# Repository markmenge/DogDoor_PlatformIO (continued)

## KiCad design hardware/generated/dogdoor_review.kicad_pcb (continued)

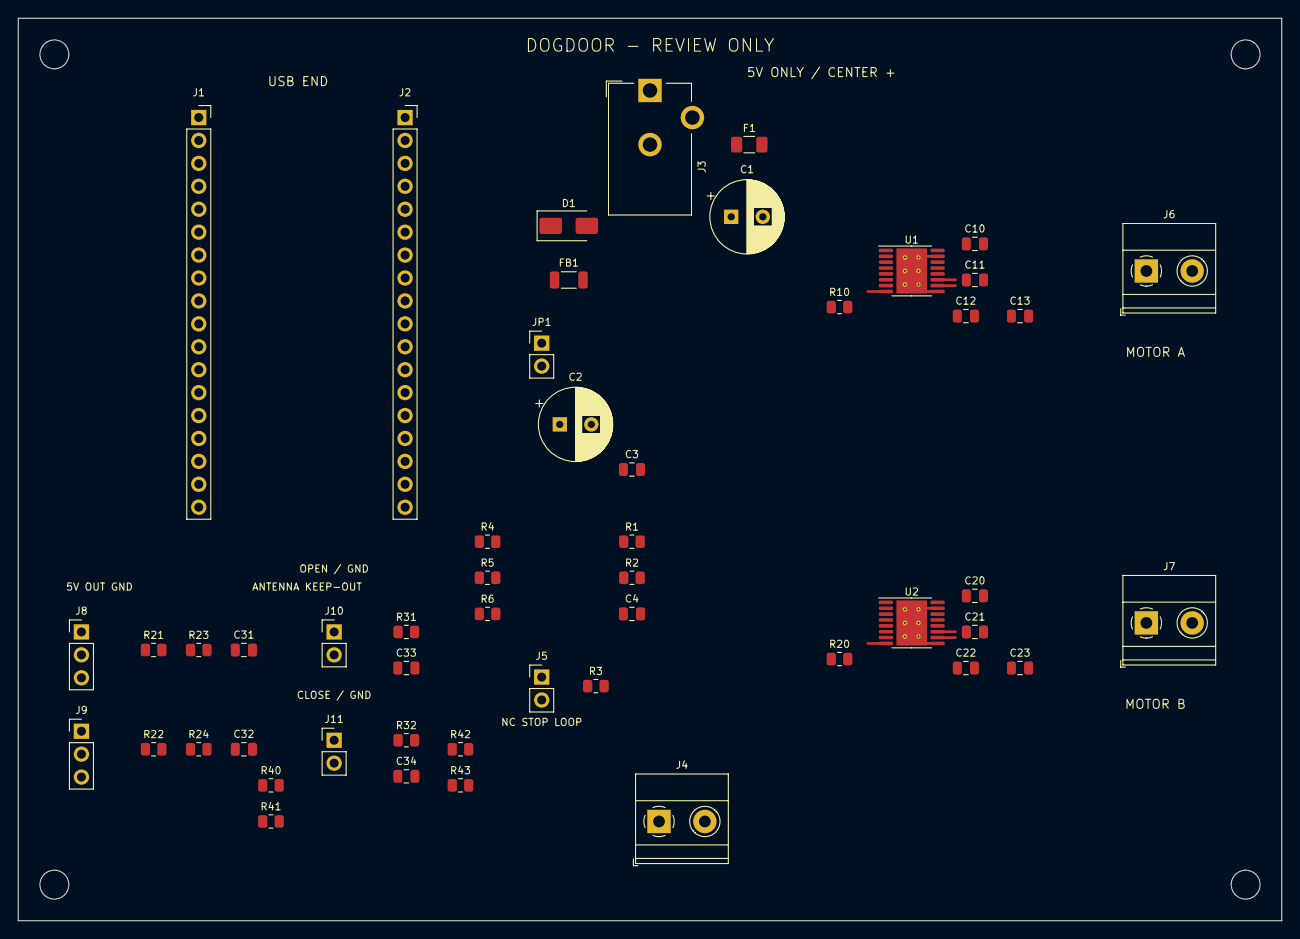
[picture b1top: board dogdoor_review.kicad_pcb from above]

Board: 2 copper layers, 140.0 x 100.0 mm, 55 parts (0 on the bottom side), 36 nets.

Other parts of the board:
H1, H2, H3, H4: MountingHole_3.2mm_M3

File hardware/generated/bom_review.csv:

Reference,Value,Footprint,Assembly,MPN,Populate
J1,Heltec V2 LEFT,Connector_PinSocket_2.54mm:PinSocket_1x18_P2.54mm_Vertical,HAND,REVIEW_REQUIRED,True
J2,Heltec V2 RIGHT,Connector_PinSocket_2.54mm:PinSocket_1x18_P2.54mm_Vertical,HAND,REVIEW_REQUIRED,True
J3,5V 3A CENTER POSITIVE,Connector_BarrelJack:BarrelJack_CUI_PJ-102AH_Horizontal,HAND,PJ-102AH,True
F1,3A fuse - inrush review,Fuse:Fuse_1206_3216Metric,SMD,0467003.NR,True
D1,SS34 controller isolation,Diode_SMD:D_SMA,SMD,SS34,True
FB1,Ferrite >=1A low DCR,Inductor_SMD:L_1206_3216Metric,SMD,REVIEW_REQUIRED,True
JP1,REMOVE FOR USB POWER,Connector_PinHeader_2.54mm:PinHeader_1x02_P2.54mm_Vertical,HAND,REVIEW_REQUIRED,True
J4,POWER ALT + GND,"TerminalBlock_Phoenix:TerminalBlock_Phoenix_MKDS-1,5-2-5.08_1x02_P5.08mm_Horizontal",HAND,REVIEW_REQUIRED,True
C1,470uF 10V low ESR,Capacitor_THT:CP_Radial_D8.0mm_P3.50mm,HAND,REVIEW_REQUIRED,True
C2,470uF 10V low ESR,Capacitor_THT:CP_Radial_D8.0mm_P3.50mm,HAND,REVIEW_REQUIRED,True
C3,100nF 25V X7R,Capacitor_SMD:C_0805_2012Metric,SMD,REVIEW_REQUIRED,True
R1,10k 1%,Resistor_SMD:R_0805_2012Metric,SMD,REVIEW_REQUIRED,True
R2,10k 1%,Resistor_SMD:R_0805_2012Metric,SMD,REVIEW_REQUIRED,True
C4,100nF 25V X7R,Capacitor_SMD:C_0805_2012Metric,SMD,REVIEW_REQUIRED,True
J5,NC STOP LOOP - OPEN DISABLES BOTH,Connector_PinHeader_2.54mm:PinHeader_1x02_P2.54mm_Vertical,HAND,REVIEW_REQUIRED,True
R3,100k,Resistor_SMD:R_0805_2012Metric,SMD,REVIEW_REQUIRED,True
R4,47k,Resistor_SMD:R_0805_2012Metric,SMD,REVIEW_REQUIRED,True
R5,47k,Resistor_SMD:R_0805_2012Metric,SMD,REVIEW_REQUIRED,True
R6,10k,Resistor_SMD:R_0805_2012Metric,SMD,REVIEW_REQUIRED,True
U1,DRV8876PWPR,Package_SO:HTSSOP-16-1EP_4.4x5mm_P0.65mm_EP3.4x5mm_Mask2.46x2.31mm_ThermalVias,SMD,DRV8876PWPR,True
C10,22nF 25V X7R,Capacitor_SMD:C_0805_2012Metric,SMD,REVIEW_REQUIRED,True
C11,100nF 25V X7R,Capacitor_SMD:C_0805_2012Metric,SMD,REVIEW_REQUIRED,True
C12,100nF 25V X7R,Capacitor_SMD:C_0805_2012Metric,SMD,REVIEW_REQUIRED,True
C13,10uF 16V X7R,Capacitor_SMD:C_0805_2012Metric,SMD,REVIEW_REQUIRED,True
R10,1.50k 1% ~1A trip,Resistor_SMD:R_0805_2012Metric,SMD,REVIEW_REQUIRED,True
J6,MOTOR A,"TerminalBlock_Phoenix:TerminalBlock_Phoenix_MKDS-1,5-2-5.08_1x02_P5.08mm_Horizontal",HAND,REVIEW_REQUIRED,True
U2,DRV8876PWPR,Package_SO:HTSSOP-16-1EP_4.4x5mm_P0.65mm_EP3.4x5mm_Mask2.46x2.31mm_ThermalVias,SMD,DRV8876PWPR,True
C20,22nF 25V X7R,Capacitor_SMD:C_0805_2012Metric,SMD,REVIEW_REQUIRED,True
C21,100nF 25V X7R,Capacitor_SMD:C_0805_2012Metric,SMD,REVIEW_REQUIRED,True
C22,100nF 25V X7R,Capacitor_SMD:C_0805_2012Metric,SMD,REVIEW_REQUIRED,True
C23,10uF 16V X7R,Capacitor_SMD:C_0805_2012Metric,SMD,REVIEW_REQUIRED,True
R20,1.50k 1% ~1A trip,Resistor_SMD:R_0805_2012Metric,SMD,REVIEW_REQUIRED,True
J7,MOTOR B,"TerminalBlock_Phoenix:TerminalBlock_Phoenix_MKDS-1,5-2-5.08_1x02_P5.08mm_Horizontal",HAND,REVIEW_REQUIRED,True
J8,PIR IN 5V OUT GND,Connector_PinHeader_2.54mm:PinHeader_1x03_P2.54mm_Vertical,HAND,REVIEW_REQUIRED,True
R21,1k,Resistor_SMD:R_0805_2012Metric,SMD,REVIEW_REQUIRED,True
R23,100k,Resistor_SMD:R_0805_2012Metric,SMD,REVIEW_REQUIRED,True
C31,100nF 25V X7R,Capacitor_SMD:C_0805_2012Metric,SMD,REVIEW_REQUIRED,True
J9,PIR OUT 5V OUT GND,Connector_PinHeader_2.54mm:PinHeader_1x03_P2.54mm_Vertical,HAND,REVIEW_REQUIRED,True
R22,1k,Resistor_SMD:R_0805_2012Metric,SMD,REVIEW_REQUIRED,True
R24,100k,Resistor_SMD:R_0805_2012Metric,SMD,REVIEW_REQUIRED,True
C32,100nF 25V X7R,Capacitor_SMD:C_0805_2012Metric,SMD,REVIEW_REQUIRED,True
J10,OPEN REED SWITCH GND,Connector_PinHeader_2.54mm:PinHeader_1x02_P2.54mm_Vertical,HAND,REVIEW_REQUIRED,True
R31,1k,Resistor_SMD:R_0805_2012Metric,SMD,REVIEW_REQUIRED,True
C33,100nF 25V X7R,Capacitor_SMD:C_0805_2012Metric,SMD,REVIEW_REQUIRED,True
J11,CLOSED REED SWITCH GND,Connector_PinHeader_2.54mm:PinHeader_1x02_P2.54mm_Vertical,HAND,REVIEW_REQUIRED,True
R32,1k,Resistor_SMD:R_0805_2012Metric,SMD,REVIEW_REQUIRED,True
C34,100nF 25V X7R,Capacitor_SMD:C_0805_2012Metric,SMD,REVIEW_REQUIRED,True
R40,0R LEGACY GPIO2,Resistor_SMD:R_0805_2012Metric,SMD,REVIEW_REQUIRED,True
R41,0R ALT GPIO22 DNP,Resistor_SMD:R_0805_2012Metric,SMD,REVIEW_REQUIRED,False
R42,0R LEGACY GPIO12,Resistor_SMD:R_0805_2012Metric,SMD,REVIEW_REQUIRED,True
R43,0R ALT GPIO27 DNP,Resistor_SMD:R_0805_2012Metric,SMD,REVIEW_REQUIRED,False

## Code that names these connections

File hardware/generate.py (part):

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    passive("R1", "10k 1%", "+3V3", "VREF", (108, 98))
    passive("R2", "10k 1%", "VREF", "GND", (108, 102))
    passive("C4", "100nF 25V X7R", "VREF", "GND", (108, 106), "C")
    component("J5", "NC STOP LOOP - OPEN DISABLES BOTH", "Connector_PinHeader_2.54mm:PinHeader_1x02_P2.54mm_Vertical",
              (98, 113), {1: "+3V3", 2: "ENABLE"}, assembly="HAND")
    passive("R3", "100k", "ENABLE", "GND", (104, 114))
    passive("R4", "47k", "OPEN", "GND", (92, 98))
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                  "TerminalBlock_Phoenix:TerminalBlock_Phoenix_MKDS-1,5-2-5.08_1x02_P5.08mm_Horizontal",
                  (165, ypos), {1: "MOTOR_" + channel + "1", 2: "MOTOR_" + channel + "2"},
                  assembly="HAND")
    for index, label, ypos, gpio in [(1, "PIR IN", 108, "PIR_IN"), (2, "PIR OUT", 119, "PIR_OUT_RAW")]:
        component("J" + str(index + 7), label + " 5V OUT GND",
                  "Connector_PinHeader_2.54mm:PinHeader_1x03_P2.54mm_Vertical",
                  (47, ypos), {1: "LOGIC_5V", 2: "PIR_RAW_" + str(index), 3: "GND"},
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        passive("R" + str(20 + index), "1k", "PIR_RAW_" + str(index), gpio, (55, ypos + 2))
        passive("R" + str(22 + index), "100k", gpio, "GND", (60, ypos + 2))
        passive("C" + str(30 + index), "100nF 25V X7R", gpio, "GND", (65, ypos + 2), "C")
    for index, label, ypos, net in [(1, "OPEN REED", 108, "LIMIT_OPEN"),
                                   (2, "CLOSED REED", 120, "CLOSE_RAW")]:
        component("J" + str(index + 9), label + " SWITCH GND",
                  "Connector_PinHeader_2.54mm:PinHeader_1x02_P2.54mm_Vertical",
                  (75, ypos), {1: "REED_RAW_" + str(index), 2: "GND"}, assembly="HAND")
        passive("R" + str(30 + index), "1k", "REED_RAW_" + str(index), net, (83, ypos))
        passive("C" + str(32 + index), "100nF 25V X7R", net, "GND", (83, ypos + 4), "C")
    passive("R40", "0R LEGACY GPIO2", "PIR_OUT_RAW", "PIR_OUT", (68, 125))
    passive("R41", "0R ALT GPIO22 DNP", "PIR_OUT_RAW", "ALT_PIR_22", (68, 129), fitted=False)
    passive("R42", "0R LEGACY GPIO12", "CLOSE_RAW", "LIMIT_CLOSE", (89, 121))
    passive("R43", "0R ALT GPIO27 DNP", "CLOSE_RAW", "ALT_CLOSE_27", (89, 125), fitted=False)
    return PARTS


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    lookup = {part["reference"]: part for part in PARTS}
    for reference in ["U1", "U2"]:
        pins = lookup[reference]["pins"]
        assert pins["1"] == "OPEN" and pins["2"] == "CLOSE"
        assert pins["11"] == "VM" and pins["16"] == "+3V3"
        assert pins["7"] is None, "IMODE must float for fixed-off-time, latched OCP"
        assert pins["9"] == pins["15"] == pins["17"] == "GND"
    assert lookup["U1"]["pins"]["8"] != lookup["U2"]["pins"]["8"]
    assert lookup["J1"]["pins"]["10"] == "OPEN"
    assert lookup["J1"]["pins"]["9"] == "CLOSE"
    assert lookup["J2"]["pins"]["2"] == "HELTEC_5V"
    assert lookup["J3"]["pins"]["1"] == "INPUT_5V"
    assert not lookup["R41"]["fitted"] and not lookup["R43"]["fitted"]
    trip = CURRENT_REFERENCE_V / (CURRENT_RESISTANCE_OHM * CURRENT_MIRROR_A_PER_A)
    assert 0.95 < trip < 1.05
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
